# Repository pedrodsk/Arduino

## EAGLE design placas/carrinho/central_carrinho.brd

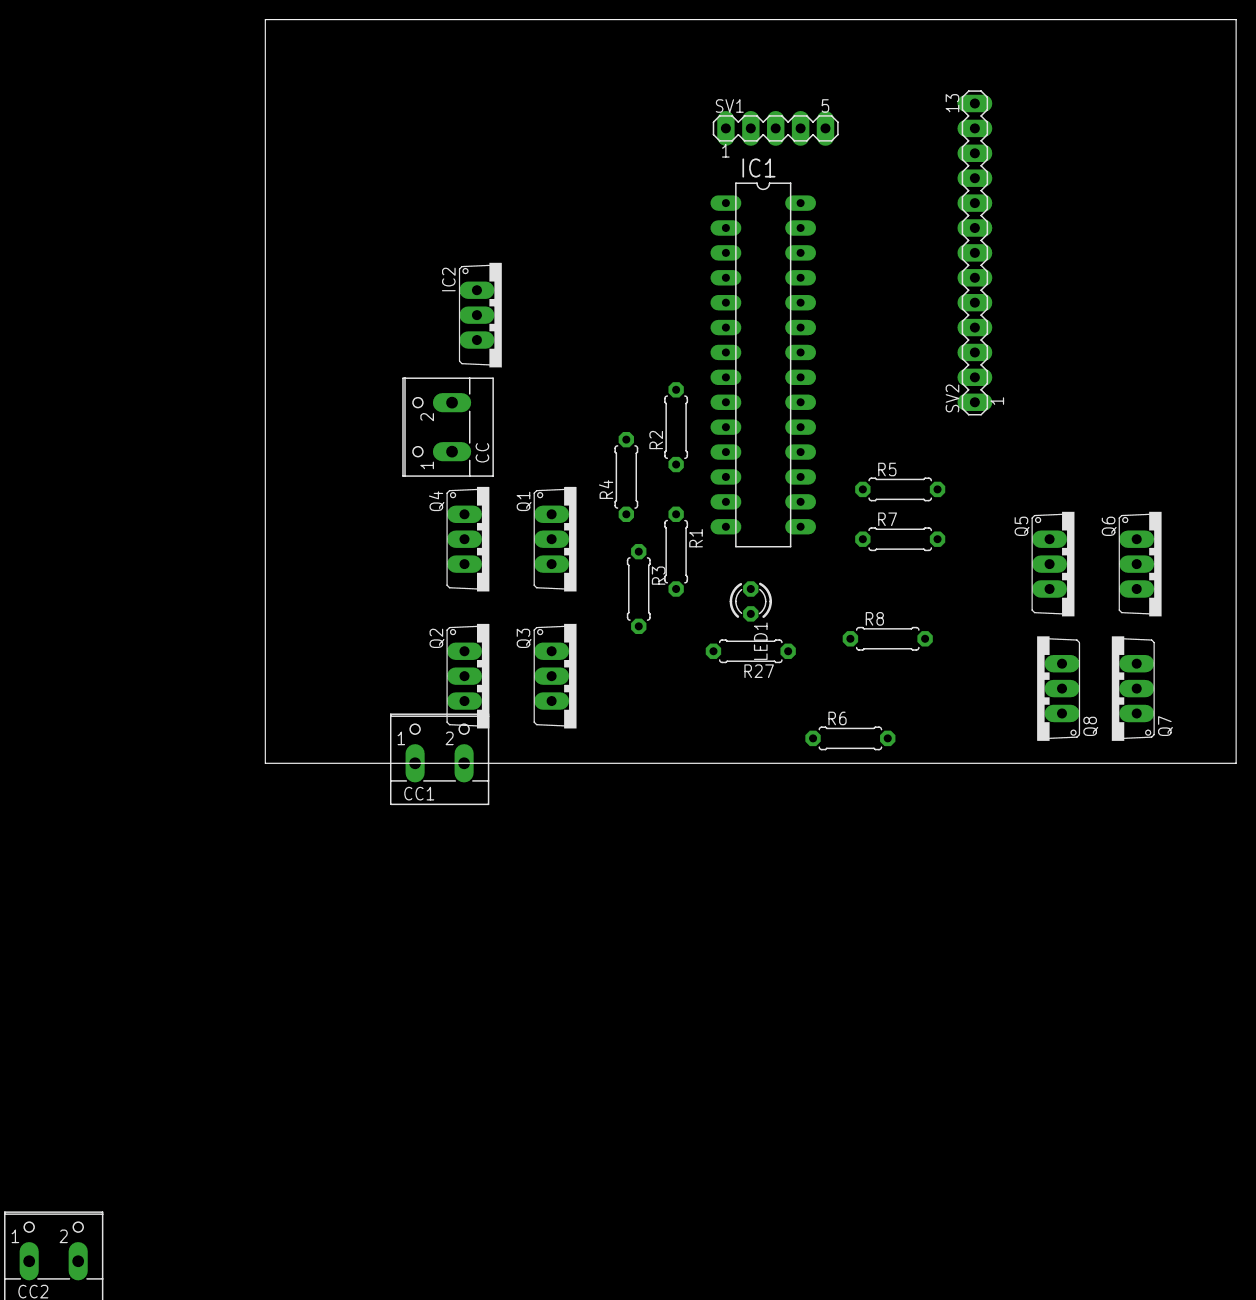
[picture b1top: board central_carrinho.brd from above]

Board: 2 copper layers, 99.0 x 75.9 mm, 25 parts (0 on the bottom side), 37 nets, no tracks yet.

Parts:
CC, CC1, CC2: W237-102
IC1: ATMEGA168-PU; DIL28-3
IC2: 7805TV; TO220V
LED1: LED3MM
Q1, Q2, Q3, Q4, Q5, Q6, Q7, Q8: TO220V
R1, R2, R3, R4, R5, R6, R7, R8: 0207/7
R27: 220; 0207/7
SV1: MA05-1
SV2: MA13-1

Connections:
A0: IC1.23, SV2.1
A1: IC1.24, SV2.2
A2: IC1.25, SV2.3
A3: IC1.26, SV2.4
A4: IC1.27, SV2.5
A5: IC1.28, SV2.6
D0: IC1.2, SV2.7
D1: IC1.3, SV2.8
D4: IC1.6, SV2.9
D5: IC1.11, R2.1, R4.1
D6: IC1.12, R1.1, R3.1
D7: IC1.13, SV2.10
D8: IC1.14, SV2.11
D9: IC1.15, R6.1, R8.1
D10: IC1.16, R5.1, R7.1
D11: IC1.17, SV2.12
D12: IC1.18, SV2.13
D13: IC1.19, LED1.A
GND: CC.1, IC1.8, IC1.22, IC2.2, Q2.3, Q3.3, Q6.3, Q7.3, R27.2, SV1.4
unnamed: Q2.1, R4.2
unnamed: Q1.1, R1.2
unnamed: Q4.1, R2.2
unnamed: Q3.1, R3.2
unnamed: Q6.1, R8.2
unnamed: Q5.1, R5.2
unnamed: LED1.K, R27.1
unnamed: Q8.1, R6.2
unnamed: Q7.1, R7.2
OUT1: CC1.1, Q1.3, Q2.2
OUT2: CC1.2, Q3.2, Q4.3
OUT3: CC2.1, Q5.3, Q6.2
OUT4: CC2.2, Q7.2, Q8.3
RESET: IC1.1, SV1.1
RX: IC1.5, SV1.2
TX: IC1.4, SV1.3
VCC: IC1.7, IC1.20, IC2.3, SV1.5
VIN: CC.2, IC2.1, Q1.2, Q4.2, Q5.2, Q8.2

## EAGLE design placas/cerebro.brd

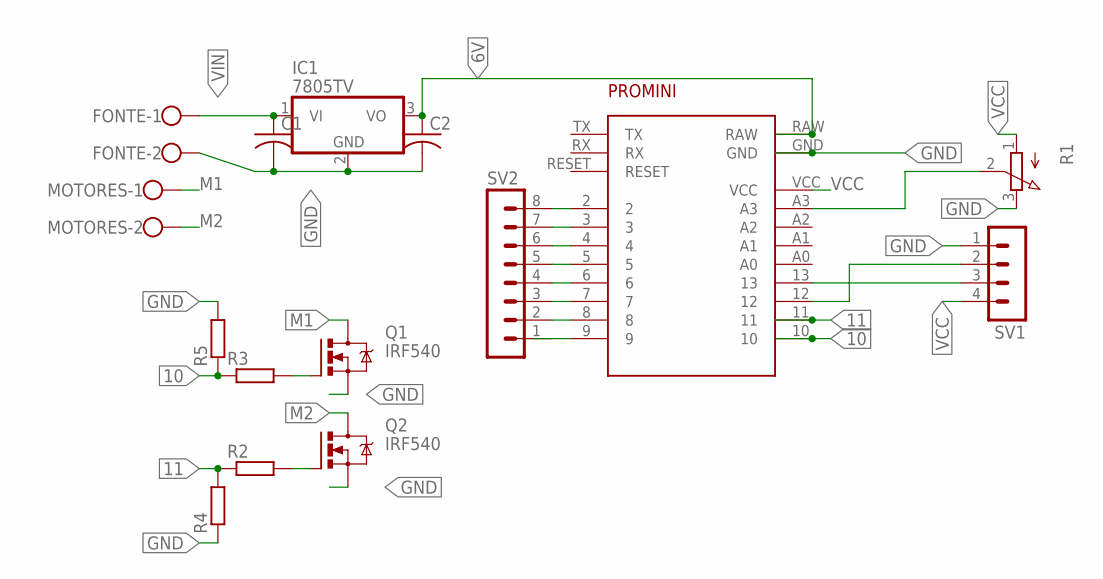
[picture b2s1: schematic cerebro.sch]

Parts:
C1, C2: C-US025-024X044; C025-024X044
FONTE: W237-102
IC1: 7805TV; TO220V
MOTORES: W237-102
Q1, Q2: IRF540; TO220BV
R1: 3RP/1610N
R2, R3, R4, R5: R-EU_0207/10; 0207/10
SV1: MA04-1
SV2: MA08-1
U$1: PROMINI; MICROCONTROLADOR

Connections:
6V: C2.1, IC1.3 (VO), U$1.RAW
10: R3.1, R5.1, U$1.10
11: R2.1, R4.2, U$1.11
GND: C1.2, C2.2, FONTE.2, IC1.2 (GND), Q1.S, Q2.S, R1.3 (E), R4.1, R5.2, SV1.1, U$1.GND
M1: MOTORES.1, Q1.D
M2: MOTORES.2, Q2.D
unnamed: R1.2 (S), U$1.A3
unnamed: Q2.G, R2.2
unnamed: SV2.2, U$1.8
unnamed: SV2.3, U$1.7
unnamed: Q1.G, R3.2
unnamed: SV2.4, U$1.6
unnamed: SV2.5, U$1.5
unnamed: SV2.6, U$1.4
unnamed: SV2.7, U$1.3
unnamed: SV2.8, U$1.2
unnamed: SV1.2, U$1.12
unnamed: SV1.3, U$1.13
VCC: R1.1 (A), SV1.4, U$1.VCC
VIN: C1.1, FONTE.1, IC1.1 (VI)

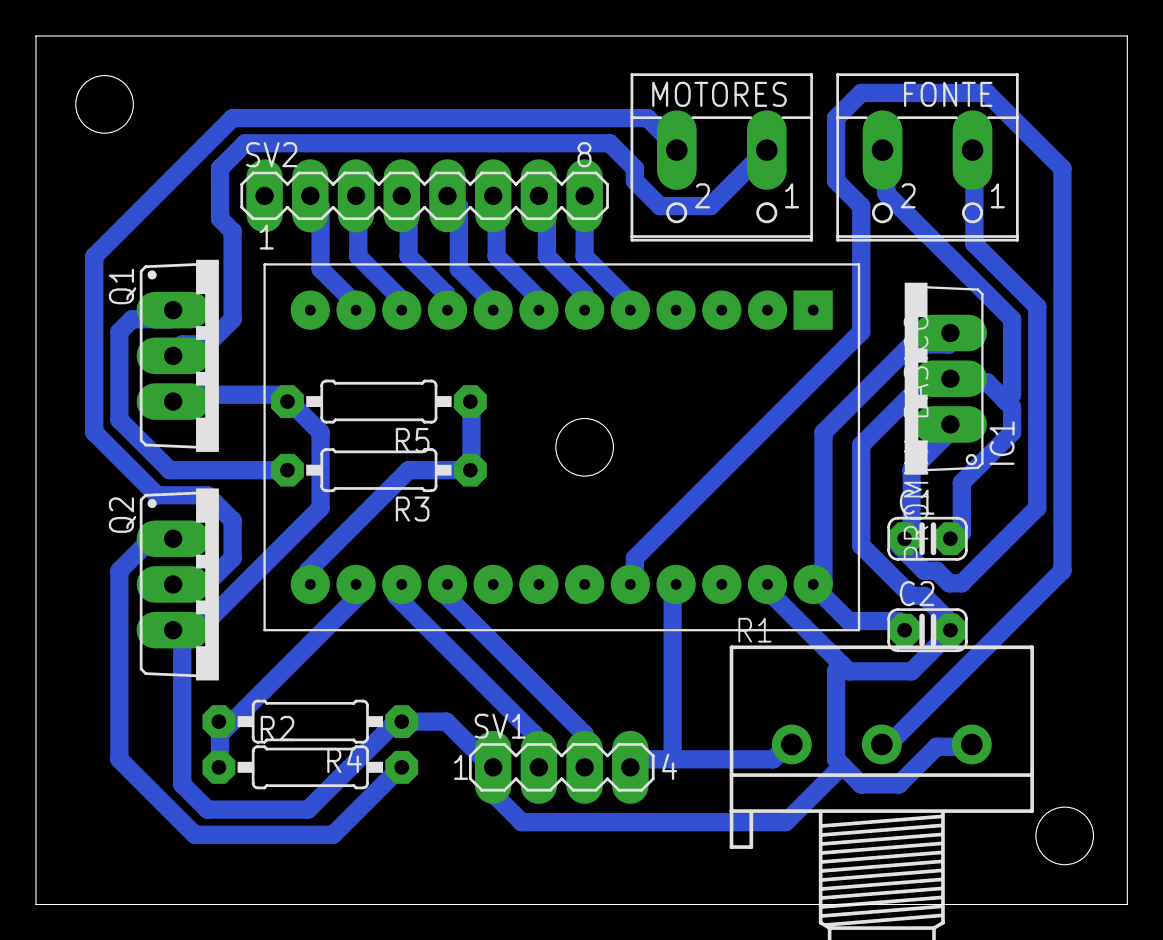
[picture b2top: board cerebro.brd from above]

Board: 1 copper layer, 60.6 x 48.2 mm, 15 parts (0 on the bottom side), 20 nets.

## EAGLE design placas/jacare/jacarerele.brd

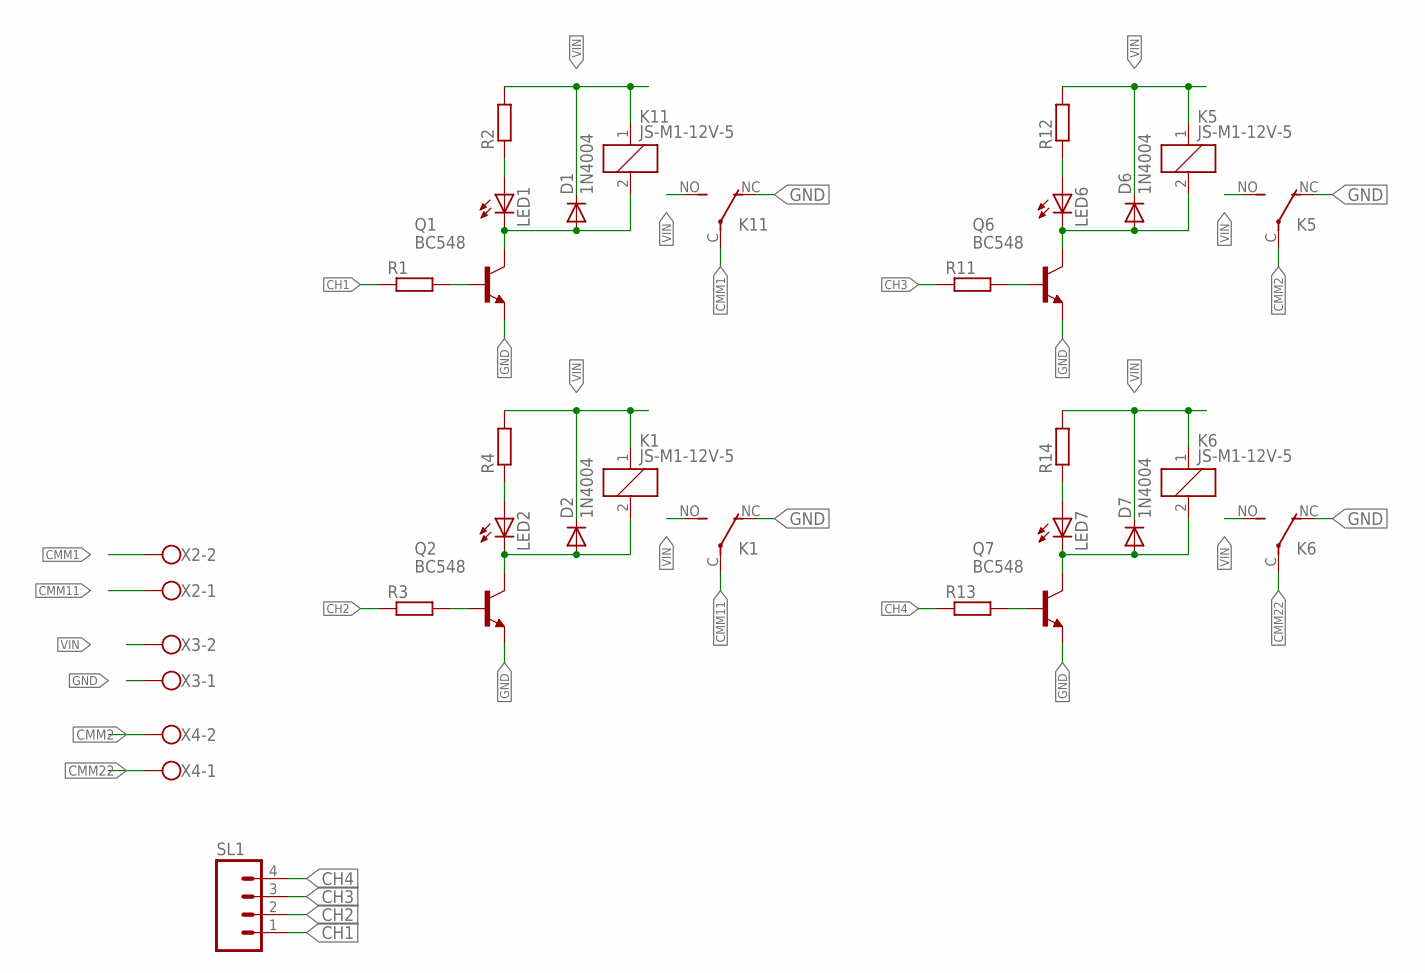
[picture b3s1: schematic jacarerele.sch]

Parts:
D1, D2, D6, D7: 1N4004; DO41-10
K1, K5, K6, K11: JS-M1-12V-5; JS-M
LED1, LED2, LED6, LED7: LED5MM
Q1, Q2, Q6, Q7: BC548; TO92-EBC
R1, R2, R3, R4, R11, R12, R13, R14: R-EU_0207/10; 0207/10
SL1: MA04; 04PA
X2, X3, X4: W237-102

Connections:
CH1: R1.1, SL1.1
CH2: R3.1, SL1.2
CH3: R11.1, SL1.3
CH4: R13.1, SL1.4
CMM1: K11.C, X2.2
CMM2: K5.C, X4.2
CMM11: K1.C, X2.1
CMM22: K6.C, X4.1
GND: K1.NC (O), K5.NC (O), K6.NC (O), K11.NC (O), Q1.E, Q2.E, Q6.E, Q7.E, X3.1
unnamed: Q1.B, R1.2
unnamed: LED1.A, R2.1
unnamed: Q2.B, R3.2
unnamed: LED2.A, R4.1
unnamed: D1.A, K11.2, LED1.K (C), Q1.C
unnamed: D2.A, K1.2, LED2.K (C), Q2.C
unnamed: Q6.B, R11.2
unnamed: LED6.A, R12.1
unnamed: D6.A, K5.2, LED6.K (C), Q6.C
unnamed: Q7.B, R13.2
unnamed: LED7.A, R14.1
unnamed: D7.A, K6.2, LED7.K (C), Q7.C
VIN: D1.C, D2.C, D6.C, D7.C, K1.1, K1.NO (S), K5.1, K5.NO (S), K6.1, K6.NO (S), K11.1, K11.NO (S), R2.2, R4.2, R12.2, R14.2, X3.2

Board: 2 copper layers, 28 parts (0 on the bottom side), 22 nets, no tracks yet.

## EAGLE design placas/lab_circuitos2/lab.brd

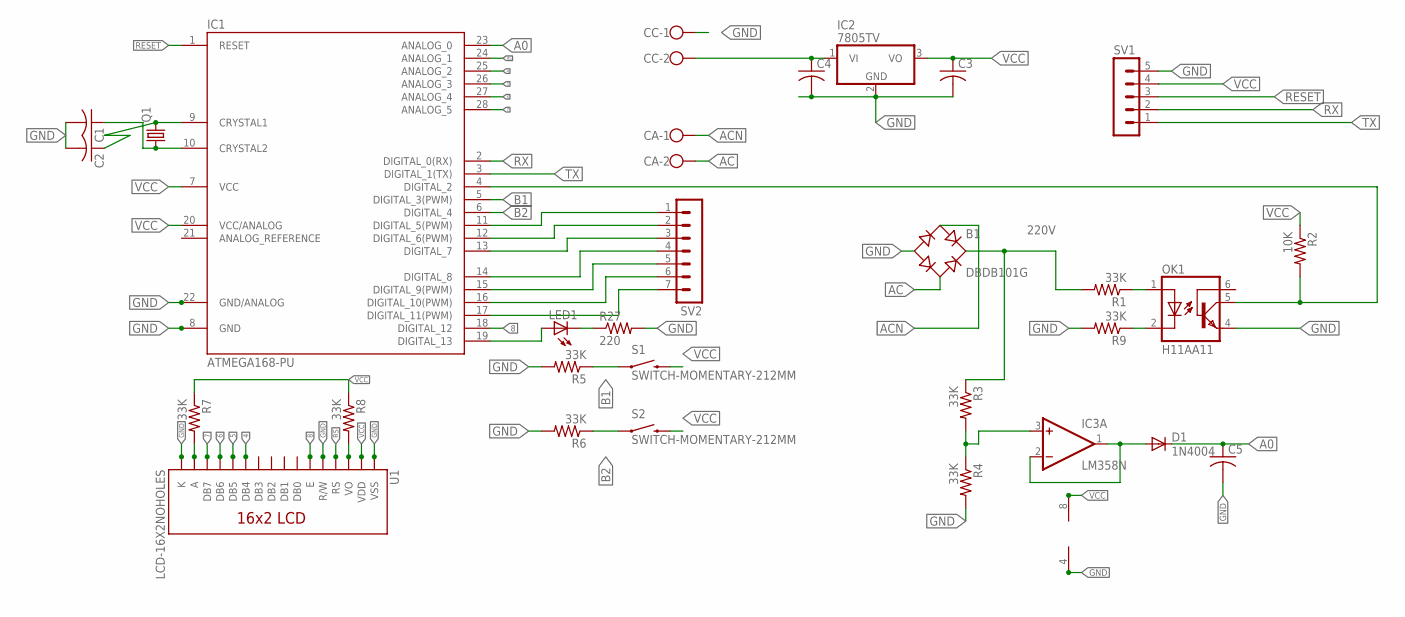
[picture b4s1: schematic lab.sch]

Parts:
B1: DBDB101G; DB
C1, C2: C-US025-025X050; C025-025X050
C3, C4, C5: C-US050-025X075; C050-025X075
CA: W237-102
CC: W237-102
D1: 1N4004; DO41-10
IC1: ATMEGA168-PU; DIL28-3
IC2: 7805TV; TO220V
IC3: LM358N; DIL08
LED1: LED3MM
OK1: H11AA11; DIL06
Q1: CRYSTALHC18U-V; HC18U-V
R1, R3, R4, R5, R6, R7, R8, R9: 33K; 0207/7
R2: 10K; 0207/7
R27: 220; 0309/10
S1, S2: SWITCH-MOMENTARY-212MM; TACTILE-PTH-12MM
SV1: MA05-1
SV2: MA07-1
U1: LCD-16X2NOHOLES; LCD-16X2_NOHOLES

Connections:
4: IC1.25 (ANALOG_2), U1.11 (DB4)
5: IC1.26 (ANALOG_3), U1.12 (DB5)
6: IC1.27 (ANALOG_4), U1.13 (DB6)
7: IC1.28 (ANALOG_5), U1.14 (DB7)
8: IC1.18 (DIGITAL_12), U1.6 (E)
220V: B1.+, R1.2, R3.1
A0: C5.1, D1.C, IC1.23 (ANALOG_0)
AC: B1.AC2, CA.2
ACN: B1.AC1, CA.1
B1: IC1.5 (DIGITAL_3(PWM)), R5.1, S1.1
B2: IC1.6 (DIGITAL_4), R6.1, S2.1
DIG02: IC1.4 (DIGITAL_2), OK1.5 (COL), R2.2
GND: B1.-, C1.2, C2.2, C3.2, C4.2, C5.2, CC.1, IC1.8 (GND), IC1.22 (GND/ANALOG), IC2.2 (GND), IC3.4 (V-), OK1.4 (EMI), R4.2, R5.2, R6.2, R9.2, R27.2, SV1.5, U1.1 (VSS), U1.5 (R/W), U1.16 (K)
unnamed: R7.2, U1.15 (A)
unnamed: D1.A, IC3.1 (OUT), IC3.2 (-IN)
unnamed: IC3.3 (+IN), R3.2, R4.1
unnamed: OK1.2 (C), R9.1
unnamed: IC1.11 (DIGITAL_5(PWM)), SV2.1
unnamed: OK1.1 (A), R1.1
unnamed: LED1.K (C), R27.1
unnamed: C2.1, IC1.9 (CRYSTAL1), Q1.2
unnamed: C1.1, IC1.10 (CRYSTAL2), Q1.1
unnamed: IC1.12 (DIGITAL_6(PWM)), SV2.2
unnamed: IC1.13 (DIGITAL_7), SV2.3
unnamed: C4.1, CC.2, IC2.1 (VI)
unnamed: IC1.14 (DIGITAL_8), SV2.4
unnamed: IC1.15 (DIGITAL_9(PWM)), SV2.5
unnamed: IC1.16 (DIGITAL_10(PWM)), SV2.6
unnamed: R8.2, U1.3 (VO)
unnamed: IC1.17 (DIGITAL_11(PWM)), SV2.7
unnamed: IC1.19 (DIGITAL_13), LED1.A
RESET: IC1.1 (RESET), SV1.3
RS: IC1.24 (ANALOG_1), U1.4 (RS)
RX: IC1.2 (DIGITAL_0(RX)), SV1.2
TX: IC1.3 (DIGITAL_1(TX)), SV1.1
VCC: C3.1, IC1.7 (VCC), IC1.20 (VCC/ANALOG), IC2.3 (VO), IC3.8 (V+), R2.1, R7.1, R8.1, S1.3 (2), S2.3 (2), SV1.4, U1.2 (VDD)

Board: 1 copper layer, 30 parts (0 on the bottom side), 36 nets, no tracks yet.

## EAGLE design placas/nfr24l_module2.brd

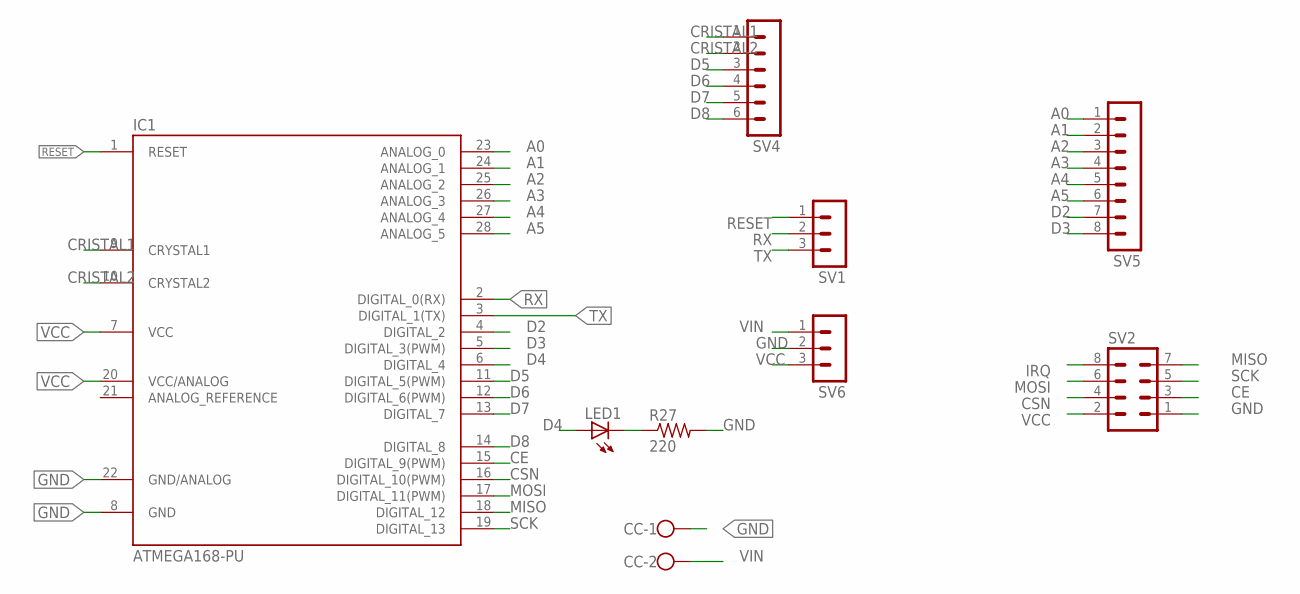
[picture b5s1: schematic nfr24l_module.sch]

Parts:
CC: W237-102
IC1: ATMEGA168-PU; DIL28-3
LED1: LED3MM
R27: 220; 0207/7
SV1, SV6: MA03-1
SV2: MA04-2
SV4: MA06-1
SV5: MA08-1

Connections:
A0: IC1.23 (ANALOG_0), SV5.1
A1: IC1.24 (ANALOG_1), SV5.2
A2: IC1.25 (ANALOG_2), SV5.3
A3: IC1.26 (ANALOG_3), SV5.4
A4: IC1.27 (ANALOG_4), SV5.5
A5: IC1.28 (ANALOG_5), SV5.6
CE: IC1.15 (DIGITAL_9(PWM)), SV2.3
CRISTAL1: IC1.9 (CRYSTAL1), SV4.1
CRISTAL2: IC1.10 (CRYSTAL2), SV4.2
CSN: IC1.16 (DIGITAL_10(PWM)), SV2.4
D2: IC1.4 (DIGITAL_2), SV5.7
D3: IC1.5 (DIGITAL_3(PWM)), SV5.8
D4: IC1.6 (DIGITAL_4), LED1.A
D5: IC1.11 (DIGITAL_5(PWM)), SV4.3
D6: IC1.12 (DIGITAL_6(PWM)), SV4.4
D7: IC1.13 (DIGITAL_7), SV4.5
D8: IC1.14 (DIGITAL_8), SV4.6
GND: CC.1, IC1.8 (GND), IC1.22 (GND/ANALOG), R27.2, SV2.1, SV6.2
IRQ: SV2.8
MISO: IC1.18 (DIGITAL_12), SV2.7
MOSI: IC1.17 (DIGITAL_11(PWM)), SV2.6
unnamed: LED1.K (C), R27.1
RESET: IC1.1 (RESET), SV1.1
RX: IC1.2 (DIGITAL_0(RX)), SV1.2
SCK: IC1.19 (DIGITAL_13), SV2.5
TX: IC1.3 (DIGITAL_1(TX)), SV1.3
VCC: IC1.7 (VCC), IC1.20 (VCC/ANALOG), SV2.2, SV6.3
VIN: CC.2, SV6.1

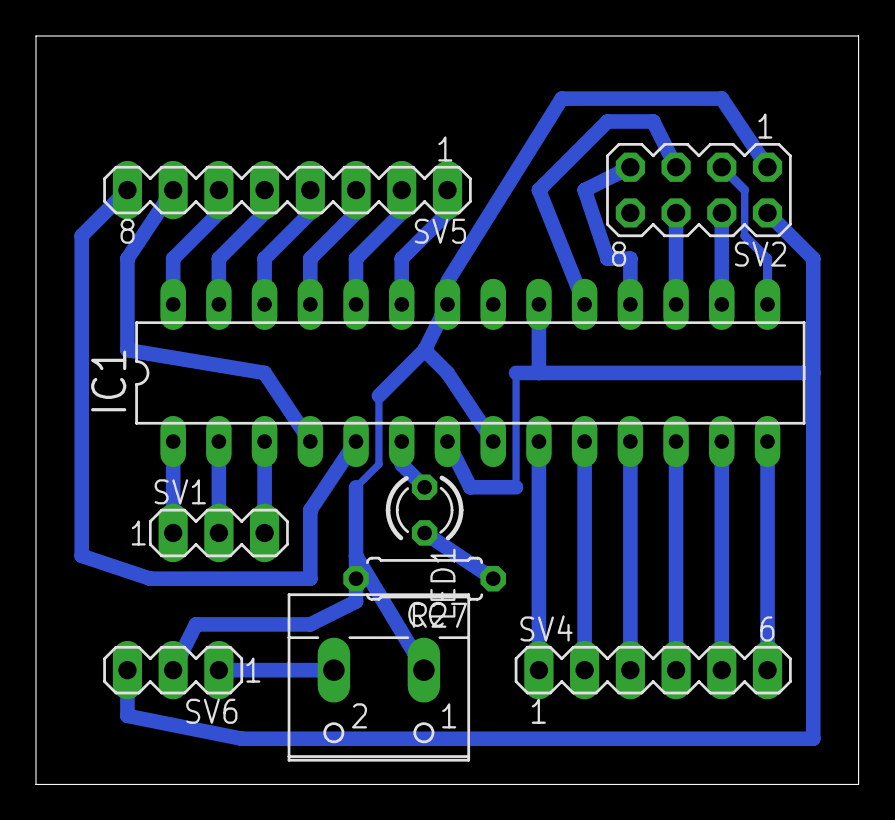
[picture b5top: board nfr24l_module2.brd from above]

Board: 2 copper layers, 45.7 x 41.6 mm, 9 parts (0 on the bottom side), 27 nets.

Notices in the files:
parts and their libraries:
SparkFun-Electromechanical: Licensing: Creative Commons ShareAlike 4.0 International - https://creativecommons.org/licenses/by-sa/4.0
